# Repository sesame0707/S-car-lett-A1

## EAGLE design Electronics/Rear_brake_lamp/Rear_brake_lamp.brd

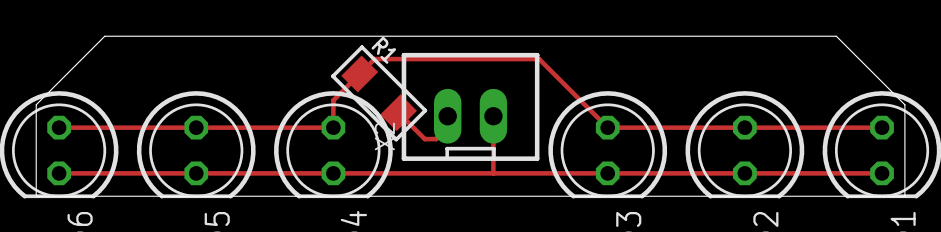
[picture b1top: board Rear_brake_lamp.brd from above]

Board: 2 copper layers, 48.3 x 8.9 mm, 8 parts (0 on the bottom side), 3 nets.

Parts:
LED1, LED2, LED3, LED4, LED5, LED6: Red; LED5MM
R1: 150; R1206
X2: JST-XH-02-PIN-LONG-PAD; JST-XH-02-PACKAGE-LONG-PAD

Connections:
API_BRAKE: LED1.A, LED2.A, LED3.A, LED4.A, LED5.A, LED6.A, R1.1
GND: LED1.K, LED2.K, LED3.K, LED4.K, LED5.K, LED6.K, X2.2
unnamed: R1.2, X2.1

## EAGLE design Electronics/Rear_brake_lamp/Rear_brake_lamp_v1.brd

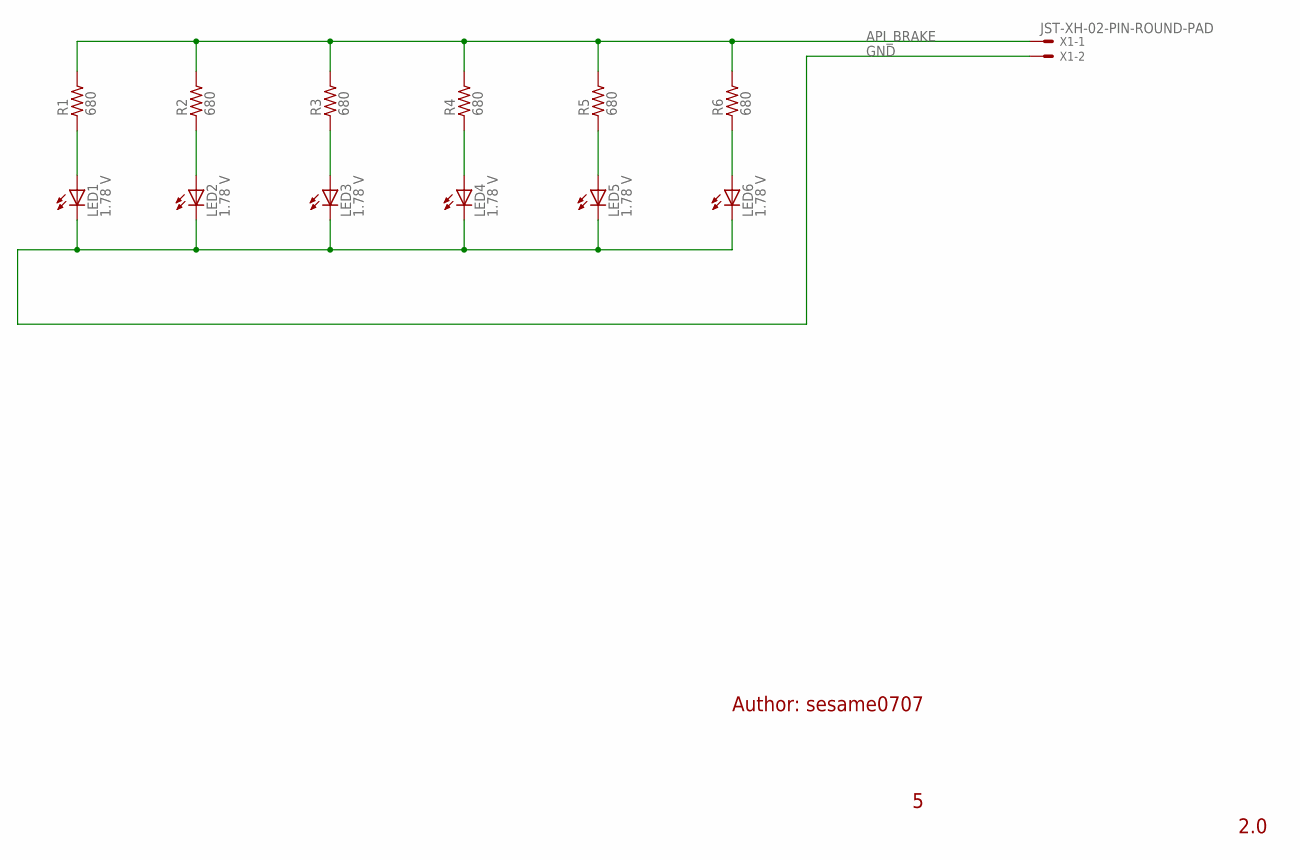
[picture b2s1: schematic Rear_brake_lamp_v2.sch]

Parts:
LED1, LED2, LED3, LED4, LED5, LED6: 1.78 V; LED5MM
R1, R2, R3, R4, R5, R6: 680; R0805
X1: JST-XH-02-PIN-ROUND-PAD; JST-XH-02-PACKAGE-ROUND-PAD

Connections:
API_BRAKE: R1.2, R2.2, R3.2, R4.2, R5.2, R6.2, X1.1
GND: LED1.K (C), LED2.K (C), LED3.K (C), LED4.K (C), LED5.K (C), LED6.K (C), X1.2
unnamed: LED1.A, R1.1
unnamed: LED2.A, R2.1
unnamed: LED3.A, R3.1
unnamed: LED4.A, R4.1
unnamed: LED5.A, R5.1
unnamed: LED6.A, R6.1

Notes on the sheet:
Author: sesame0707
2.0

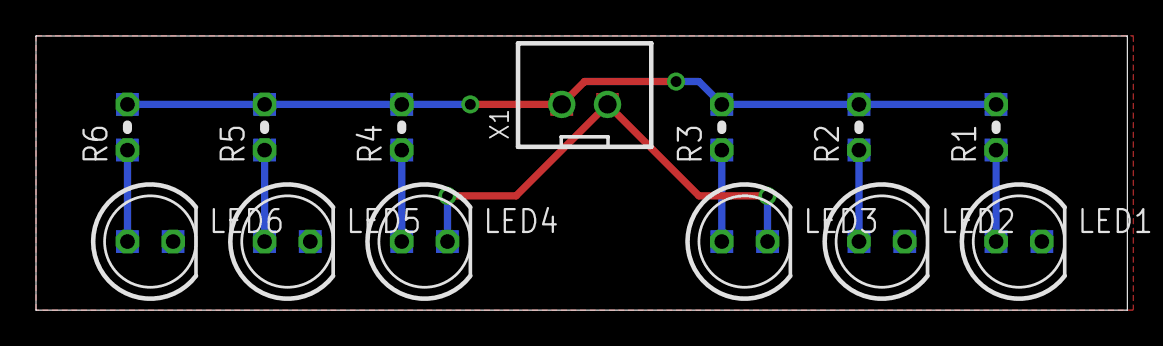
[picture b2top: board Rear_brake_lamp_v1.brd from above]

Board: 2 copper layers, 60.6 x 15.2 mm, 13 parts (0 on the bottom side), 8 nets.

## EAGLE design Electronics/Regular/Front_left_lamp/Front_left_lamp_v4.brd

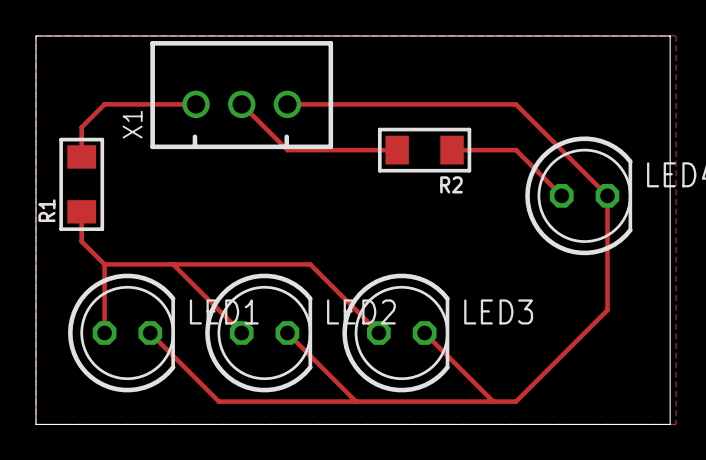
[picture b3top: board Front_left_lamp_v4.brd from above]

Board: 2 copper layers, 35.2 x 21.6 mm, 7 parts (0 on the bottom side), 5 nets.

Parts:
LED1, LED2, LED3: 2.58 V; LED5MM
LED4: 1.88 V; LED5MM
R1: 1K5; R1206
R2: 680; R1206
X1: JST-XH-03-PIN-ROUND-PAD; JST-XH-03-PACKAGE-ROUND-PAD

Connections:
API_START_ENGINE: LED1.A, LED2.A, LED3.A, R1.1
API_TURN_LEFT: R2.2, X1.2
GND: LED1.K, LED2.K, LED3.K, LED4.K, X1.3
unnamed: R1.2, X1.1
unnamed: LED4.A, R2.1

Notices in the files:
parts and their libraries:
rc-master-smd: Copyright (C) 2007, Bob Starr
